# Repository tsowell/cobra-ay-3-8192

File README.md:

(Vezi [README-ro.md](README-ro.md) pentru o traducere greșită în română.)

# AY-3-8192 interface for Cobra

This is a simple AY-3-8192 interface for the expansion port of the Romanian
microcomputer Cobra.

The interface logic is based on the logic in the [Simple AY interface by
hw.speccy.cz][Simple AY interface], and the output mixing is
based on the Spectrum 128K.

The board has an input for the Cobra's beeper output and mixes it with the
AY-3-8192 output.

NOTE: This revision has not been tested yet.  It includes some simple fixes for
problems in the [previous revision][0da03c1], which is known to work.

[Simple AY interface]: https://hw.speccy.cz/ayinterface.html

[0da03c1]: https://github.com/tsowell/cobra-ay-3-8192/tree/0da03c1

## Images

(shown with bodges)

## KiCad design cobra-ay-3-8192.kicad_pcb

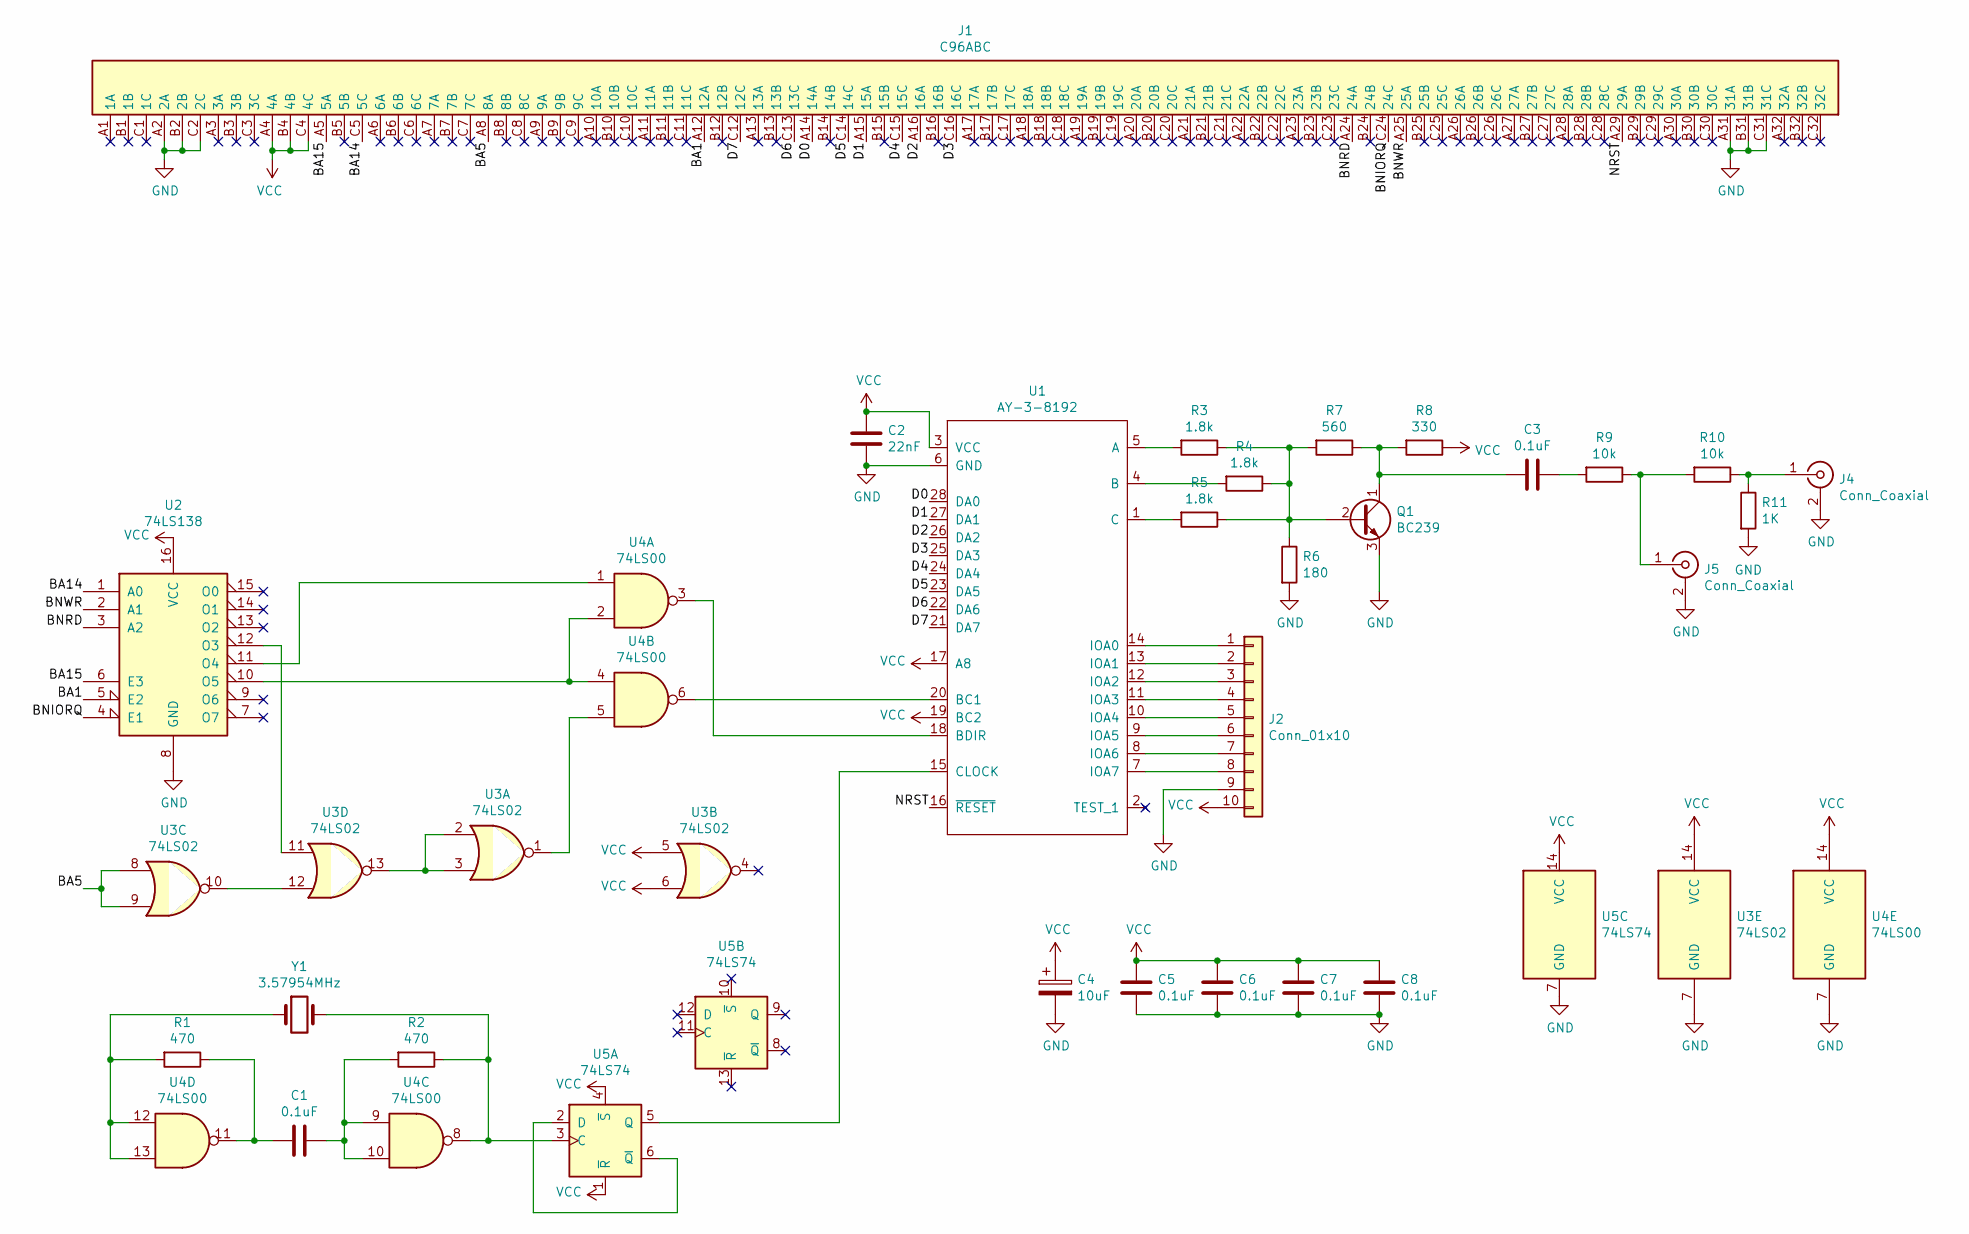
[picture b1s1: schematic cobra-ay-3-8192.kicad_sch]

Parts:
C1, C3, C5, C6, C7, C8: 0.1uF; C_Disc_D5.0mm_W2.5mm_P5.00mm
C2: 22nF; C_Disc_D5.0mm_W2.5mm_P5.00mm
C4: 10uF; CP_Radial_D5.0mm_P2.50mm
J1: C96ABC; DIN41612_C_3x32_Female_Horizontal_THT
J2: Conn_01x10; PinHeader_1x10_P2.54mm_Vertical
J4, J5: Conn_Coaxial; RCJ-04
Q1: BC239; TO-92_Inline_Wide
R1, R2: 470; R_Axial_DIN0204_L3.6mm_D1.6mm_P7.62mm_Horizontal
R3, R4, R5: 1.8k; R_Axial_DIN0204_L3.6mm_D1.6mm_P7.62mm_Horizontal
R6: 180; R_Axial_DIN0204_L3.6mm_D1.6mm_P7.62mm_Horizontal
R7: 560; R_Axial_DIN0204_L3.6mm_D1.6mm_P7.62mm_Horizontal
R8: 330; R_Axial_DIN0204_L3.6mm_D1.6mm_P7.62mm_Horizontal
R9, R10: 10k; R_Axial_DIN0204_L3.6mm_D1.6mm_P7.62mm_Horizontal
R11: 1K; R_Axial_DIN0204_L3.6mm_D1.6mm_P7.62mm_Horizontal
U1: AY-3-8192; DIP-28_W15.24mm_Socket
U2: 74LS138; DIP-16_W7.62mm_Socket
U3: 74LS02; DIP-14_W7.62mm_Socket
U4: 74LS00; DIP-14_W7.62mm_Socket
U5: 74LS74; DIP-14_W7.62mm_Socket
Y1: 3.57954MHz; Crystal_HC49-U_Vertical

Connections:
/BA1: J1.A12 (12A), U2.5 (E2)
/BA5: J1.A8 (8A), U3.8, U3.9
/BA14: J1.C5 (5C), U2.1 (A0)
/BA15: J1.A5 (5A), U2.6 (E3)
/BNIORQ: J1.C24 (24C), U2.4 (E1)
/BNRD: J1.A24 (24A), U2.3 (A2)
/BNWR: J1.A25 (25A), U2.2 (A1)
/D0: J1.A14 (14A), U1.28 (DA0)
/D1: J1.A15 (15A), U1.27 (DA1)
/D2: J1.A16 (16A), U1.26 (DA2)
/D3: J1.C16 (16C), U1.25 (DA3)
/D4: J1.C15 (15C), U1.24 (DA4)
/D5: J1.C14 (14C), U1.23 (DA5)
/D6: J1.C13 (13C), U1.22 (DA6)
/D7: J1.C12 (12C), U1.21 (DA7)
/NRST: J1.A29 (29A), U1.16 (~RESET)
GND: C2.2, C4.2, C5.2, C6.2, C7.2, C8.2, J1.A2 (2A), J1.A31 (31A), J1.B2 (2B), J1.B31 (31B), J1.C2 (2C), J1.C31 (31C), J2.9, J4.2 (Ext), J5.2 (Ext), Q1.3 (E), R6.2, R11.2, U1.6 (GND), U2.8 (GND), U3.7 (GND), U4.7 (GND), U5.7 (GND)
unnamed: C1.1, R2.2, U4.9, U4.10
unnamed: C1.2, R1.1, U4.11
unnamed: C3.1, R9.2
unnamed: C3.2, Q1.1 (C), R7.1, R8.2
unnamed: J2.1, U1.14 (IOA0)
unnamed: J2.2, U1.13 (IOA1)
unnamed: J2.3, U1.12 (IOA2)
unnamed: J2.4, U1.11 (IOA3)
unnamed: J2.5, U1.10 (IOA4)
unnamed: J2.6, U1.9 (IOA5)
unnamed: J2.7, U1.8 (IOA6)
unnamed: J2.8, U1.7 (IOA7)
unnamed: J5.1 (In), R9.1, R10.2
unnamed: Q1.2 (B), R3.1, R4.1, R5.1, R6.1, R7.2
unnamed: R1.2, U4.12, U4.13, Y1.1
unnamed: R2.1, U4.8, U5.3 (C), Y1.2
unnamed: R3.2, U1.5 (A)
unnamed: R4.2, U1.4 (B)
unnamed: R5.2, U1.1 (C)
unnamed: J4.1 (In), R10.1, R11.1
unnamed: U1.15 (CLOCK), U5.5 (Q)
unnamed: U1.18 (BDIR), U4.3
unnamed: U1.20 (BC1), U4.6
unnamed: U2.10 (O5), U4.2, U4.4
unnamed: U2.11 (O4), U4.1
unnamed: U2.12 (O3), U3.11
unnamed: U3.1, U4.5
unnamed: U3.10, U3.12
unnamed: U3.2, U3.3, U3.13
unnamed: U5.2 (D), U5.6 (~Q)
VCC: C2.1, C4.1, C5.1, C6.1, C7.1, C8.1, J1.A4 (4A), J1.B4 (4B), J1.C4 (4C), J2.10, R8.1, U1.3 (VCC), U1.17 (A8), U1.19 (BC2), U2.16 (VCC), U3.5, U3.6, U3.14 (VCC), U4.14 (VCC), U5.1 (~R), U5.4 (~S), U5.14 (VCC)

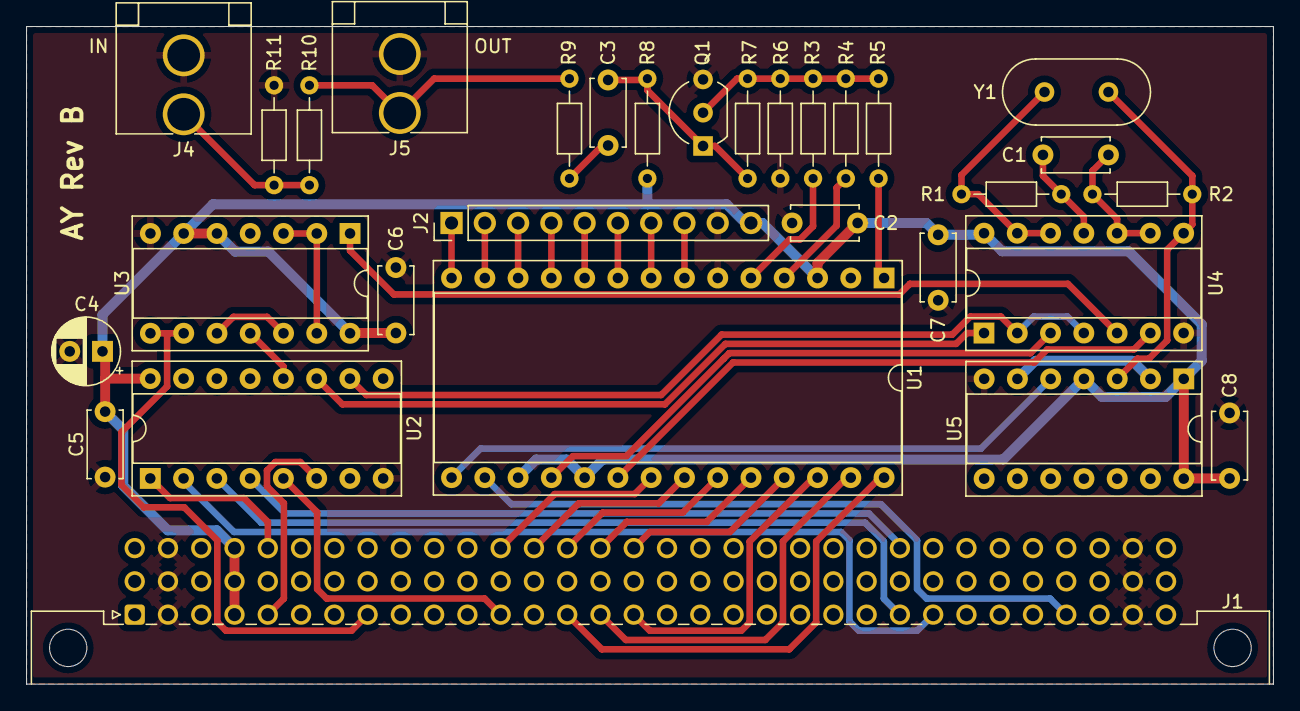
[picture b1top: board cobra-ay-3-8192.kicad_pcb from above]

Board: 2 copper layers, 95.2 x 50.2 mm, 30 parts (0 on the bottom side), 48 nets.

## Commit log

2022-01-26 Fix issues with audio input/output
    Swap RCA connector pins, move RCA connectors closer to board edge, and
    add resistors R10 and R11 to input audio.
